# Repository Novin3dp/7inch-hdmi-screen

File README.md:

# برد راه‌انداز LCD هفت اینچ AT070TN92 با ورودی HDMI و تاچ USB

برد دولایه‌ی کوچک (۸۰×۵۰ میلی‌متر) که پشت LCD چسبانده می‌شود:

* **ورودی HDMI** (از رزبری‌پای) ← **LT8619C** ← RGB موازی ۲۴ بیتی (حالت DE) ← کانکتور FPC پنجاه‌پین **AT070TN92**
* **تاچ خازنی GT915** (روی FPC تاچ‌پنل، رابط I2C) ← **STM32F072** ← **USB HID Multi-Touch** (۵ نقطه) به رزبری‌پای
* **تغذیه‌ی کل برد از همان کابل USB-C** (۵ ولت از پورت USB رزبری‌پای)
* تولید ولتاژهای پنل روی برد: AVDD=10.4V، VGH=+16V، VGL=−6.8V، VCOM قابل تنظیم، درایور بک‌لایت جریان‌ثابت ۱۸۰ mA با PWM

> ⚠️ این طراحی کامل است و همه‌ی بررسی‌های نرم‌افزاری (DRC، تطبیق شماتیک با PCB، کامپایل فرم‌ور، اعتبارسنجی EDID) را پاس کرده، اما **هنوز ساخته و روی سخت‌افزار تست نشده است**. قبل از سفارش انبوه، یک نمونه بسازید و بخش «موارد قابل بررسی» را بخوانید.

> **نسخه‌ی DSI:** یک برد جداگانه (۶۸×۴۲ mm) هم هست که همین پنل و تاچ را مستقیم از پورت DSI رزبری‌پای و با پل ICN6211 راه می‌اندازد، بدون HDMI و بدون میکروکنترلر. طراحی در [`hardware_dsi/`](hardware_dsi/README.md) و Overlay و درایور لینوکس در `rpi_dsi/` است.
>
> **نسخه‌ی دو-میکرو:** همین برد HDMI با یک جای نصب LQFP-48 که هم STM32F072 و هم CH32X035C8T6 رویش می‌نشیند: [`hardware_dual/`](hardware_dual/README.md).
>
> **نسخه‌ی STM32F042F6P6:** همین برد HDMI با میکروی کوچک‌تر TSSOP-20 در [`hardware_f042/`](hardware_f042/README.md). فرم‌ور با `make BOARD=f042` ساخته می‌شود.

---

## ۱) بلوک دیاگرام

```
 HDMI-A ──TMDS──► LT8619C ──RGB888 + DE + PCLK──► J3 (FPC 50P) ──► AT070TN92
   │ DDC/HPD        ▲ I2C1 (0x32)                       ▲ AVDD/VGH/VGL/VCOM, VLED
   └─(EDID روی تراشه)│                                    │
                    STM32F072 ──── BIAS_EN ──► TPS61040 + پمپ‌های بار + LM321 (VCOM)
 USB-C ◄──USB FS──► │ ──── BL_PWM ───► TPS61165 (بک‌لایت ۱۸۰mA)
   │5V              │ ──── I2C2 ────► J4 (FPC 6P) ──► تاچ‌پنل GT915
   └► PTC ► AMS1117-3.3 / AMS1117-1.8 (+ فیلتر فریت برای تغذیه‌های آنالوگ LT8619C)
```

| بخش | قطعه | توضیح |
|---|---|---|
| گیرنده HDMI | LT8619C (QFN76) | کریستال 25MHz، EDID داخلی 800×480@60 که میکرو بارگذاری می‌کند؛ VTERM/VCCA33 و 1.8V آنالوگ با فریت جدا شده‌اند |
| میکرو | STM32F072CBT6 | USB بدون کریستال (HSI48 + CRS)، بوت‌لودر DFU داخلی |
| بایاس پنل | TPS61040 + 2×BAT54S + زنر | AVDD 10.4V، VGH 16V (دوبرابرکننده)، VGL −6.8V (معکوس‌کننده) |
| VCOM | LM321 + تریمر 10k (RV1) | محدوده 2.55 تا 4.5 ولت، برای کمترین فلیکر تنظیم شود |
| بک‌لایت | TPS61165 | 0.2V / 1.1Ω = 182mA، PWM با فرکانس 20kHz |
| تغذیه | AMS1117-3.3 و AMS1117-1.8 | هر دو از 5V؛ 1.8V با فریت به تغذیه‌های آنالوگ |

---

## ۲) ساختار ریپازیتوری

```
hardware/                 پروژه‌ی KiCad (نسخه 7)
  lcd_board.kicad_pro/.kicad_sch/.kicad_pcb    پروژه، شماتیک سلسله‌مراتبی (۴ صفحه)، PCB
  lcd_board.pretty/       فوت‌پرینت‌های اختصاصی (QFN76 لونتیوم، FPC پنجاه‌پین)
  lcd_board.kicad_sym     سمبل LT8619C
  fab/                    فایل‌های ساخت: gerber.zip، BOM و CPL برای JLCPCB
  gen/                    اسکریپت‌هایی که کل طراحی را می‌سازند (منبع اصلی = design.py)
firmware/                 فرم‌ور STM32F072 (C + TinyUSB)
hardware_dual/            همین برد HDMI با جای نصب مشترک STM32F072 / CH32X035C8T6
hardware_f042/            همین برد HDMI با STM32F042F6P6 — پروژه‌ی KiCad جدا با README خودش
hardware_dsi/             نسخه‌ی DSI (ICN6211) — پروژه‌ی KiCad جدا با README خودش
rpi_dsi/                  Device Tree Overlay و اسکریپت ساخت درایور ICN6211 برای نسخه‌ی DSI
docs/                     schematic.pdf، schematic_f042.pdf، schematic_dsi.pdf و تصاویر برد
*.pdf                     دیتاشیت‌ها
```

**منبع اصلی طراحی فایل `hardware/gen/design.py` است** (لیست قطعات و همه‌ی اتصالات). شماتیک، PCB و BOM از روی آن ساخته می‌شوند و `verify_netlist.py` تطابق شماتیک و طراحی را بررسی می‌کند. البته می‌توانید فایل‌های KiCad را مستقیم هم ویرایش کنید.

---

## ۳) مشخصات PCB

| مورد | مقدار |
|---|---|
| ابعاد | 80 × 50 mm، گوشه‌های گرد R2 |
| لایه | ۲ لایه، FR4، ضخامت پیشنهادی 1.0 یا 1.6 mm، مس 1oz |
| حداقل ترک/فاصله | 0.15 / 0.15 mm (تغذیه 0.25 و 0.5 mm) |
| ویا | سوراخ 0.3 / قطر 0.6 mm (ظرفیت استاندارد JLCPCB) |
| قطعات | **فقط روی رو (Top)**؛ پشت برد صاف است برای چسب دوطرفه |
| زمین | GND به‌صورت نت کامل مسیریابی شده + پور GND روی هر دو لایه + ~۳۰۰ ویای دوخت |
| DRC | **۰ خطای الکتریکی/فاصله و ۰ اتصال باز**؛ برچسب‌های سیلک بدون تداخل (هشدار فقط برای خطوط سیلک کانکتورهای لبه‌ی برد که سازنده برش می‌دهد) |
| سیلک‌اسکرین | برچسب‌ها با ارتفاع 0.8mm خودکار کنار هر قطعه گذاشته شده‌اند، روی پد/بدنه‌ی قطعه یا برچسب دیگر نمی‌افتند. ۱۳ برچسب در نواحی خیلی شلوغ جا نشدند و فقط در نقشه‌ی مونتاژ (`docs/img/pcb_assembly.png`) آمده‌اند |

نکات چیدمان:
* زوج‌های TMDS (HDMI) دستی و کوتاه (~۱۲ mm) کشیده شده‌اند و زیرشان لایه‌ی پشت زمین یکپارچه است. سرعت هر کانال برای 800×480 فقط 333Mbps است.
* خازن‌های دکاپلینگ پایه‌های VTERM/VCCA33 بین زوج‌های TMDS قرار گرفته‌اند.
* ترتیب پایه‌های RGB در LT8619C نسبت به FPC پنل وارونه است؛ گذرگاه RGB با ویا روی دو لایه جابه‌جا شده (بدون نیاز به رجیستر نامستند جابه‌جایی بیت).

---

## ۴) نصب مکانیکی و جهت FPC (مهم)

* FPC پنل (۳۰ میلی‌متر) از لبه‌ی پایین LCD به پشت تا می‌شود و از **لبه‌ی پایین برد** وارد J3 می‌شود. کنتاکت‌های FPC در این حالت رو به بالا (دور از برد) هستند، پس J3 باید **کانکتور Top-contact** باشد — همان چیزی که دیتاشیت Innolux پیشنهاد کرده: `Hirose FH12A-50S-0.5SH`.
* شماره‌ی پدهای J3 دقیقاً برابر شماره‌ی پین‌های FPC پنل است؛ **پین ۱ سمت راست** است (برد از رو، FPC از پایین وارد شود). همین جهت برای حالت تا‌نخورده (برد زیر پنل) هم درست است.
* برد را با **چسب دوطرفه‌ی فومی عایق** (۱ میلی‌متر) پشت پنل بچسبانید؛ پشت پنل فلزی است و ویاها با سولدرماسک پوشیده‌اند ولی عایق اضافه لازم است.
* J4 (FPC شش‌پین 0.5mm تاچ) هم روی لبه‌ی پایین است. ترتیب پین‌ها طبق مدار مرجع Goodix: `1 GND, 2 VDD(3.3V), 3 INT, 4 SCL, 5 SDA, 6 RST`. **ترتیب پین FPC تاچ‌پنل خودتان را حتماً چک کنید**؛ اگر فرق دارد، به یک تبدیل FPC یا تغییر ترتیب پین‌های J4 در `design.py` نیاز است.
* HDMI از لبه‌ی چپ و USB-C از لبه‌ی راست خارج می‌شوند.

---

## ۵) تغذیه و مصرف

| مصرف‌کننده | تقریبی |
|---|---|
| بک‌لایت (9.3V × 180mA ÷ راندمان) | ~2.0 W |
| LT8619C (1.8V و 3.3V، از LDO) | ~1.1 W از 5V |
| بایاس پنل + منطق + میکرو + تاچ | ~0.4 W |
| **جمع** | **~3.5 W ≈ 0.7 A از 5V** |

پورت‌های USB رزبری‌پای ۴ و ۵ این جریان را می‌دهند (مجموعاً 1.2A/1.6A). با کم کردن نور بک‌لایت مصرف کم می‌شود. فیوز PTC (1.1A) روی VBUS است.

ترتیب روشن شدن (طبق بخش 3.2 دیتاشیت پنل، توسط فرم‌ور):
`DVDD(3.3V) → آزاد شدن RESET → BIAS_EN (VGL و AVDD، سپس VGH با تأخیر RC) → داده‌ی تصویر → بعد از 200ms بک‌لایت`.
بک‌لایت فقط وقتی تصویر معتبر از HDMI دریافت می‌شود روشن است.

---

## ۶) ساخت برد (JLCPCB)

1. `hardware/fab/lcd_board_gerbers.zip` را برای ساخت PCB آپلود کنید (2 لایه).
2. برای مونتاژ: `hardware/fab/bom_jlcpcb.csv` و `hardware/fab/cpl_jlcpcb.csv`.
   * شماره‌های LCSC فقط برای قطعاتی که مطمئن بودم پر شده‌اند؛ بقیه را با MPN/مقدار جستجو کنید.
   * LT8619C معمولاً در LCSC نیست؛ از فروشنده‌های لونتیوم (مثلاً بازار چین) تهیه و دستی لحیم کنید (QFN76 با پد زیرین: هیتر هوای گرم/استنسیل).
   * چرخش‌ها در CPL را در پیش‌نمایش JLC کنترل کنید.
3. قطعات نصب‌نشده (DNP): J5 (هدر SWD/UART)، نقاط تست TP1..TP8.
4. همه‌ی مقاومت‌ها و خازن‌های کوچک پکیج **0603** هستند (لحیم دستی راحت). فقط چند خازن که به ظرفیت/ولتاژ بالا نیاز دارند 0805/1206 مانده‌اند (22µF، 4.7µF/25V، 1µF/50V، 2.2µF/50V) و مقاومت حسگر جریان بک‌لایت 0805 است.

---

## ۷) فرم‌ور

```sh
cd firmware
./fetch_deps.sh        # TinyUSB 0.17 + هدرهای CMSIS
make                   # نیاز به arm-none-eabi-gcc ؛ خروجی build/lcd_touch.bin
make flash-dfu         # دکمه‌ی BOOT را نگه دارید و USB را وصل کنید (dfu-util لازم است)
```

برای برد دو-میکرو با CH32X035C8T6: `./fetch_deps.sh ch32 && make BOARD=ch32` (جزئیات در `hardware_dual/README.md`). برای برد F042: `make BOARD=f042`.

کارهایی که فرم‌ور انجام می‌دهد:
* ترتیب روشن شدن پنل و کنترل بک‌لایت
* راه‌اندازی LT8619C: ریست، خواندن Chip ID (0x16 0x04)، بارگذاری EDID (800×480@60Hz، 33.26MHz)، HPD، پیکربندی گیرنده و خروجی RGB888 SDR، تبدیل رنگ YCbCr→RGB، کپی تایمینگ ورودی به خروجی
* انتخاب آدرس GT915 (0x5D) با ترتیب INT/RESET دیتاشیت، خواندن رزولوشن تنظیم‌شده‌ی تاچ و مقیاس‌کردن به 800×480
* دستگاه USB HID «Touch Screen» پنج‌نقطه‌ای؛ لینوکس (hid-multitouch) بدون درایور اضافه می‌شناسد
* کنسول UART (پین‌های 5 و 6 هدر J5، 115200): دستورات `status`، `bl 0..100`، `phase 0..9`، `rot 0|1`، `swap`، `invx`، `invy`، `save`
* تنظیمات (نور، چرخش ۱۸۰ درجه، جهت تاچ، فاز PCLK) در فلش ذخیره می‌شوند

---

## ۸) تنظیم رزبری‌پای

با Raspberry Pi OS (KMS) معمولاً هیچ تنظیمی لازم نیست: EDID برد حالت 800×480 را اعلام می‌کند و تاچ به‌صورت خودکار شناخته می‌شود. اگر تصویر نیامد، در `/boot/firmware/cmdline.txt` اضافه کنید:

```
video=HDMI-A-1:800x480M@60
```

و برای Pi های قدیمی (درایور غیر KMS) در `config.txt`:

```
hdmi_group=2
hdmi_mode=87
hdmi_cvt=800 480 60 6 0 0 0
hdmi_drive=1
```

برای چرخاندن ۱۸۰ درجه بهتر است از دستور `rot 1` کنسول برد استفاده کنید (پنل و تاچ هر دو در سخت‌افزار برمی‌گردند).

---

## ۹) موارد قابل بررسی و ریسک‌ها (لطفاً بخوانید)

1. **LT8619C سند رسمی رجیستر ندارد.** توالی رجیسترها از درایورهای متن‌باز (Hardkernel u-boot و درایور V4L2 راک‌چیپ) گرفته شده و برای خروجی RGB888 کار کرده است. اگر رنگ‌ها لرزش/نویز داشتند فاز PCLK را با `phase 0..9` تغییر دهید. برای تولید، از Lontium (support@lontium.com) شماتیک مرجع و Programming Guide بخواهید.
2. در گزارش موجود در ریپازیتوری گفته شده که خطوط TMDS با خازن 100nF کوپل AC شوند؛ **این برای HDMI درست نیست** — TMDS کوپل DC است و ترمینیشن به 3.3V از پایه‌های VTERM می‌آید. در این برد اتصال مستقیم است.
3. جهت FPC پنل و نوع کانکتور Top-contact (بخش ۴) را قبل از لحیم کنترل کنید.
4. ترتیب پین FPC تاچ‌پنل شما ممکن است با ترتیب مرجع Goodix فرق داشته باشد.
5. GT915 برای پنل‌های ۴.۵ تا ۶ اینچ طراحی شده؛ پیکربندی (Config) آن را سازنده‌ی تاچ‌پنل در فلش آی‌سی ذخیره کرده است. اگر محورها برعکس بود با `swap/invx/invy` اصلاح کنید.
6. VCOM هر پنل باید با RV1 برای کمترین فلیکر تنظیم شود (نقطه‌ی تست TP7). مقدار معمول طبق دیتاشیت ~3.6V.
7. محافظ ESD روی خطوط TMDS عمداً حذف شده تا مسیرها کوتاه و تمیز بمانند (سیگنال‌ها مستقیم به LT8619C می‌روند).
8. پین‌اوت آی‌سی‌ها از کتابخانه‌ی رسمی KiCad برداشته شده و پین‌اوت TPS61040 و TPS61165 با دیتاشیت TI چک شد؛ فوت‌پرینت QFN76 از ابعاد صفحه 16 دیتاشیت LT8619C ساخته شده (پد زیرین 5.81×6.31mm).
9. VID/PID USB از `pid.codes` (آزمایشی 1209:0001) است؛ برای محصول تجاری عوض کنید.

---

## ۱۰) ساخت دوباره‌ی طراحی از اسکریپت‌ها

نیازمندی‌ها: KiCad 7 (`kicad-cli` و ماژول پایتون `pcbnew`)، Java و Xvfb برای Freerouting.

```sh
cd hardware/gen
python3 make_libs.py                 # فوت‌پرینت/سمبل اختصاصی
python3 gen_sch.py                   # شماتیک
python3 verify_netlist.py            # تطبیق شماتیک با design.py
python3.12 pcb.py                    # چیدمان + مسیرهای دستی (TMDS، USB، VCOM، I2C و تغذیه آنالوگ LT8619C)
python3.12 route.py export           # فایل DSN برای Freerouting
java -jar freerouting-2.0.1.jar --gui.enabled=false -de ../lcd_board.dsn -do ../lcd_board.ses -mp 100
python3.12 route.py import ../lcd_board.ses   # مسیرها + پورها + ویاهای دوخت
python3.12 check.py --fill           # پر کردن پورها و DRC
python3 fab.py                       # گربر، BOM، CPL، تصاویر و PDF شماتیک
```

فایل `hardware/lcd_board.ses` (خروجی Freerouting که برد فعلی از آن ساخته شده) در ریپازیتوری هست، پس بدون اجرای دوباره‌ی Freerouting هم `route.py import` همین برد را می‌سازد.

## مجوز

سخت‌افزار: CERN-OHL-P v2. فرم‌ور: GPL-2.0-or-later (چون توالی LT8619C از کد GPL گرفته شده).

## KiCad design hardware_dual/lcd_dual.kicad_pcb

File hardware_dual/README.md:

# HDMI7 دو-میکرو: STM32F072CBT6 یا CH32X035C8T6 روی یک جای نصب

این پروژه همان برد HDMI7 اصلی (`hardware/`، 80×50mm) است، با **USB-C در لبه‌ی چپ، درست زیر سوکت HDMI** (هر دو کابل رزبری‌پای از یک طرف خارج می‌شوند؛ آی‌سی ESD یعنی U4 روی مسیر USB به سمت میکرو است)، با یک فوت‌پرینت LQFP-48 (U10) که **هر دو میکرو** روی آن می‌نشینند. اول STM32F072 را نصب و برد را تست کنید، بعد آن را با هوای گرم بردارید و CH32X035C8T6 را جایش لحیم کنید.

> ⚠️ همه‌ی بررسی‌های نرم‌افزاری پاس شده‌اند (DRC بدون خطا و بدون اتصال باز، تطبیق شماتیک با PCB، کامپایل فرم‌ور هر دو میکرو)، ولی برد و فرم‌ور CH32 **هنوز روی سخت‌افزار تست نشده‌اند**.

## چرا یک فوت‌پرینت کافی است

پایه‌های اصلی دو تراشه در LQFP-48 یکی‌اند:

| پایه | STM32F072 | CH32X035C8T6 |
|---|---|---|
| 7 | NRST | PA21/RST |
| 32 / 33 | USB D− / D+ | USB D− / D+ |
| 34 / 37 | SWDIO / SWCLK | SWDIO / SWCLK |
| 47 / 48 | VSS / VDD | GND / VDD |

همه‌ی سیگنال‌های برد روی CH32 هم به یک GPIO قابل استفاده می‌رسند:

| پایه | سیگنال | STM32F072 | CH32X035 |
|---|---|---|---|
| 10 | HDMI5V_DET | PA0 | PA0 |
| 16 | BL_PWM | PA6 (TIM3_CH1) | PA6 (TIM3_CH1) |
| 18 / 19 / 20 | LCD_RST / LR / UD | PB0 / PB1 / PB2 | PC6 / PC7 / PB0 |
| 21 / 22 | TP_SCL / TP_SDA | PB10 / PB11 (I2C2) | PB1 / PB2 (I2C نرم‌افزاری) |
| 25 / 26 | TP_INT / TP_RST | PB12 / PB13 | PB5 / PB6 |
| 28 / 29 | LED / BIAS_EN | PB15 / PA8 | PB8 / PB9 |
| 30 / 31 | UART TX / RX | PA9 / PA10 (USART1) | PB10 / PB11 (USART1) |
| 41 | LT_RSTN | PB5 | PA9 |
| 42 / 43 | LT_SCL / LT_SDA | PB6 / PB7 (I2C1) | PA10 / PA11 (I2C نرم‌افزاری) |
| 44 | BOOT0 | BOOT0 | PA12 (استفاده نمی‌شود) |

I2C روی CH32 نرم‌افزاری است، چون I2C سخت‌افزاری آن در بعضی سری‌های تولید ایراد دارد.

**نکته‌ی مهم برای فرم‌ور CH32:** پایه‌های تغذیه‌ی STM32 (۱، ۸، ۹، ۲۳، ۲۴، ۳۵، ۳۶) روی CH32 پایه‌ی GPIO هستند (PA15، PA22، PA23، PB3، PB4، PB12، PB13) که به 3.3V یا زمین وصل شده‌اند. فرم‌ور CH32 **هرگز نباید این پایه‌ها را خروجی کند**؛ بعد از ریست ورودی هستند و همین‌طور باید بمانند.

## بوت‌لودر

* **STM32F072:** دکمه‌ی SW1 (BOOT0) را نگه دارید و USB را وصل کنید ← DFU.
* **CH32X035:** دکمه‌ی SW2 را نگه دارید و USB را وصل کنید. SW2 پایه‌ی D+ (PC17) را از طریق R38 (4.7k) به 3.3V می‌برد و تراشه وارد بوت‌لودر USB می‌شود (WCHISPTool یا `wchisp`). برنامه‌ریزی با WCH-LinkE روی هدر J5 (SWDIO/SWCLK) هم ممکن است. SW2 روی STM32 بی‌اثر است.

## فرم‌ور

هر دو میکرو از همان کد `firmware/` استفاده می‌کنند؛ فقط لایه‌ی سخت‌افزار (کلاک، GPIO، PWM، UART، فلش، I2C) جداست (`firmware/src/stm32/` و `firmware/src/ch32/`).

```sh
cd firmware
./fetch_deps.sh ch32          # SDK رسمی WCH (EVT) + TinyUSB master (درایور USB برای CH32X035)
make                          # STM32F072  -> build/lcd_touch.bin
make BOARD=ch32               # CH32X035C8T6 -> build_ch32/lcd_touch_ch32.bin  (28.9KB فلش، ~5KB رم)
make BOARD=ch32 flash-isp     # بوت‌لودر USB (SW2 را هنگام وصل کردن USB نگه دارید)، با wchisp
make BOARD=ch32 flash-wlink   # یا با WCH-LinkE روی J5
```

کامپایلر RISC-V لازم است: `riscv-none-elf-gcc` (xPack) یا در اوبونتو `gcc-riscv64-unknown-elf` + `picolibc-riscv64-unknown-elf`.

تفاوت‌های نسخه‌ی CH32:
* هر دو باس I2C نرم‌افزاری (bit-bang) هستند: LT8619C حدود 100kHz و GT915 حدود 250kHz، با پشتیبانی از clock stretching و آزادسازی باس گیرکرده در شروع.
* USB: کنترلر USBFS داخلی، بدون کریستال، مقاومت pull-up داخلی روی D+ و PHY در حالت 3.3V.
* تنظیمات در آخرین صفحه‌ی ۲۵۶ بایتی فلش (0x0800F700) ذخیره می‌شوند.
* دستورهای کنسول (`status`، `bl`، `phase`، `rot`، ...) و رفتار برد همان نسخه‌ی STM32 است.

## تعویض میکرو

1. با STM32F072 و فرم‌ور `firmware/` (`make`) برد را کامل تست کنید.
2. STM32 را با هوای گرم بردارید، پدها را با فتیله تمیز کنید.
3. CH32X035C8T6 را با **همان جهت پایه‌ی ۱** لحیم کنید.

## بک‌لایت: TPS61169DCKR

در این برد درایور بک‌لایت **TPS61169DCKR** (پکیج SC70-5) است، به‌جای TPS61165 در برد اصلی:

| مورد | مقدار |
|---|---|
| پایه‌ها | 1 SW، 2 GND، 3 FB، 4 CTRL، 5 VIN |
| جریان LED | 204mV / R31 (1.13Ω) ≈ **۱۸۰mA** |
| PWM روشنایی | 20kHz از میکرو روی CTRL (مجاز طبق دیتاشیت: 5 تا 100kHz) |
| خاموشی | CTRL بیش از 2.5ms پایین ← خاموش |
| قطعات اطراف | سلف 10µH (مجاز 4.7 تا 10µH)، دیود MBR0560، خازن خروجی 2.2µF/50V (مجاز 1 تا 10µF) |

خازن جبران‌سازی (C44 در برد اصلی) حذف شده، چون TPS61169 جبران‌سازی داخلی دارد. فرم‌ور تغییری لازم ندارد.

## ساخت

**ویاها:** همه‌ی ۴۶۳ ویا سوراخ 0.4mm و قطر بیرونی 0.7mm هستند (حلقه‌ی مسی 0.15mm). ویاهای حرارتی زیر LT8619C جزء فوت‌پرینت‌اند و همان 0.3/0.6 مانده‌اند.

`fab/lcd_dual_gerbers.zip`، `fab/bom_jlcpcb.csv` (با STM32F072)، `fab/cpl_jlcpcb.csv`؛ شماتیک: `docs/schematic_dual.pdf`. برای ساخت دوباره، اسکریپت‌های `hardware_dual/gen` مثل بخش ۱۰ README اصلی اجرا می‌شوند.

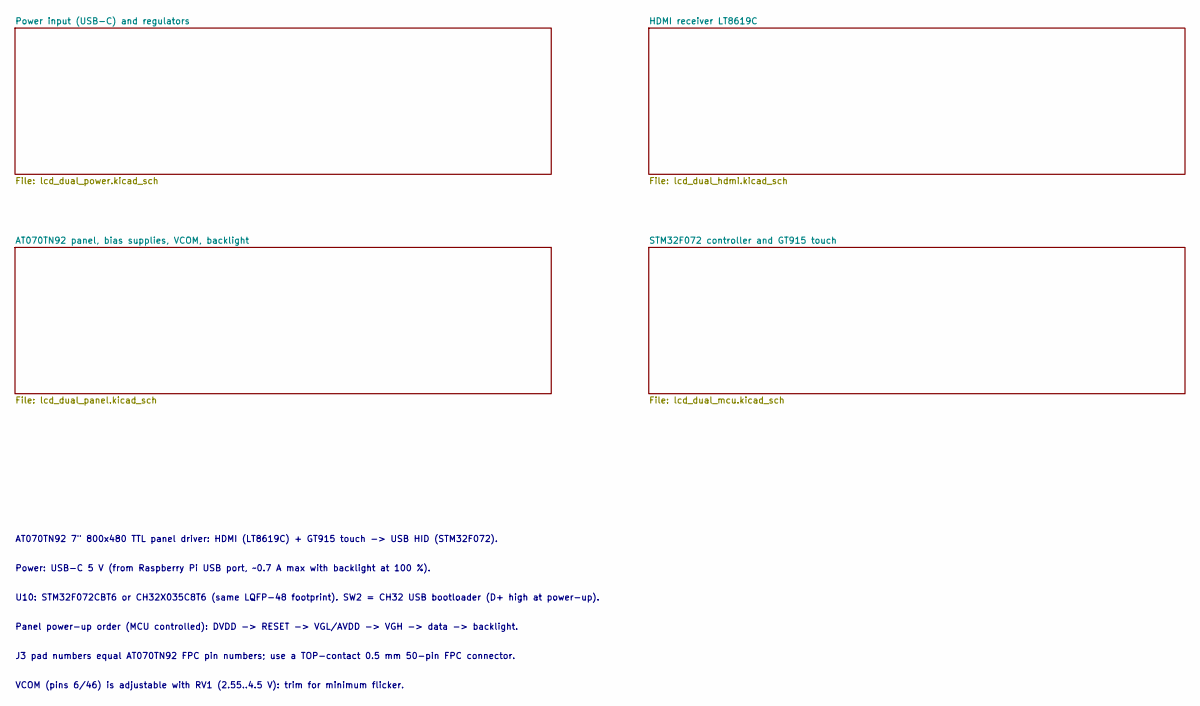
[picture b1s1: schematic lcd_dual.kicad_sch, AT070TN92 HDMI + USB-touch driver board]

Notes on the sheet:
AT070TN92 7" 800x480 TTL panel driver: HDMI (LT8619C) + GT915 touch -> USB HID (STM32F072).
Power: USB-C 5 V (from Raspberry Pi USB port, ~0.7 A max with backlight at 100 %).
U10: STM32F072CBT6 or CH32X035C8T6 (same LQFP-48 footprint). SW2 = CH32 USB bootloader (D+ high at power-up).
Panel power-up order (MCU controlled): DVDD -> RESET -> VGL/AVDD -> VGH -> data -> backlight.
J3 pad numbers equal AT070TN92 FPC pin numbers; use a TOP-contact 0.5 mm 50-pin FPC connector.
VCOM (pins 6/46) is adjustable with RV1 (2.55..4.5 V): trim for minimum flicker.

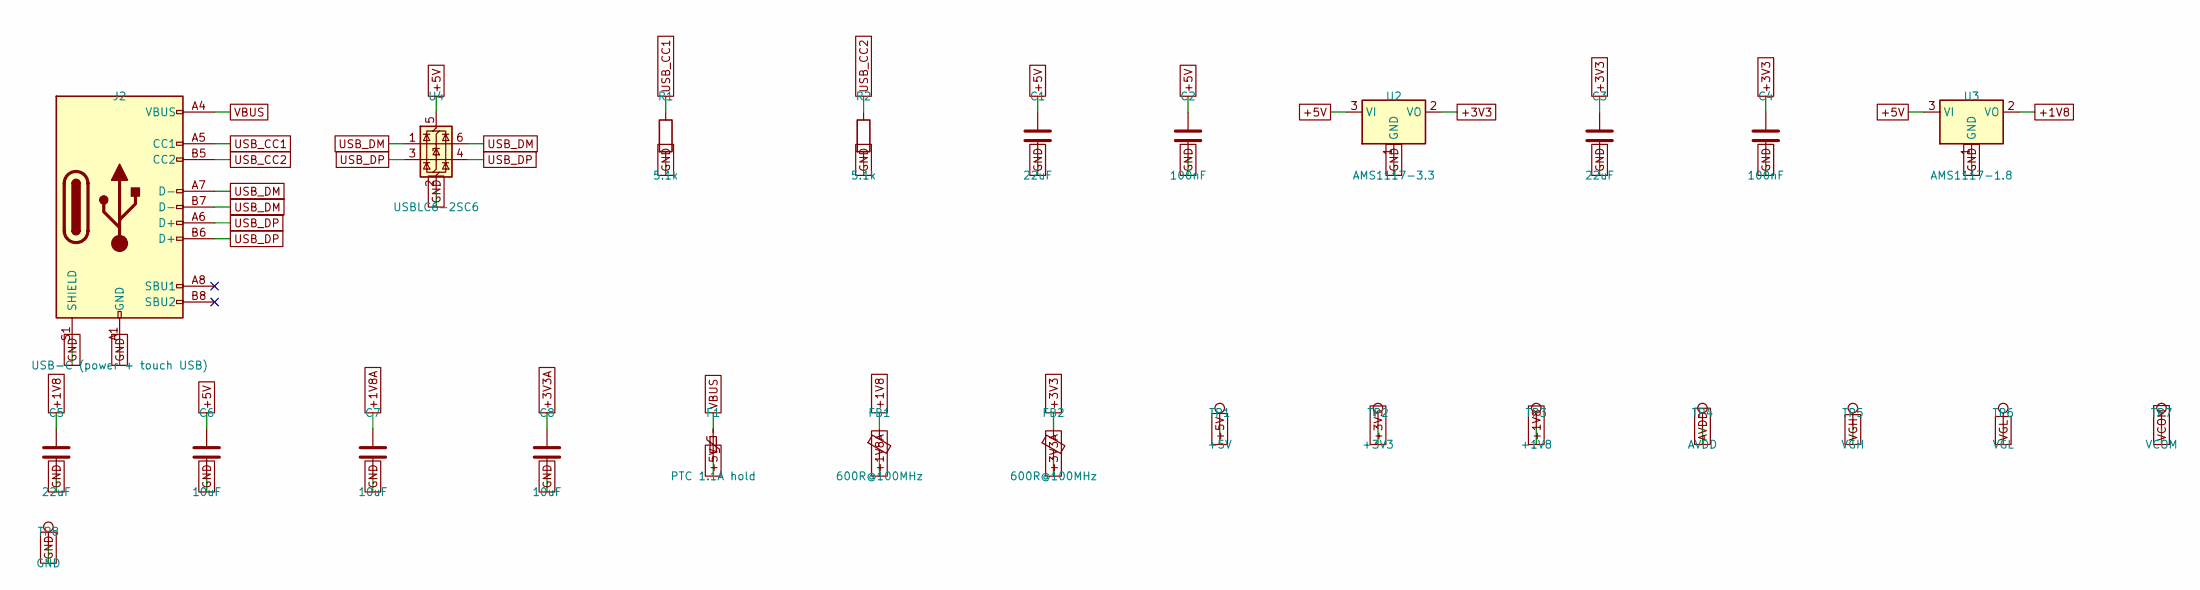
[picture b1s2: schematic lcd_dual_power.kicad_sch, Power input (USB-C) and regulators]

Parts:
C1, C3, C5: 22uF; C_0805_2012Metric
C2, C4: 100nF; C_0603_1608Metric; LCSC C14663
C6, C7, C8: 10uF; C_0603_1608Metric; LCSC C19702
F1: PTC 1.1A hold; Fuse_1206_3216Metric; MPN 1206L110/16 (or BSMD1206-110)
FB1, FB2: 600R@100MHz; L_0603_1608Metric; MPN BLM18PG601SN1D
J2: USB-C (power + touch USB); USB_C_Receptacle_HRO_TYPE-C-31-M-12; MPN HRO TYPE-C-31-M-12; LCSC C165948
R1, R2: 5.1k; R_0603_1608Metric; LCSC C23186
TP1: +5V; TestPoint_Pad_D1.0mm
TP2: +3V3; TestPoint_Pad_D1.0mm
TP3: +1V8; TestPoint_Pad_D1.0mm
TP4: AVDD; TestPoint_Pad_D1.0mm
TP5: VGH; TestPoint_Pad_D1.0mm
TP6: VGL; TestPoint_Pad_D1.0mm
TP7: VCOM; TestPoint_Pad_D1.0mm
TP8: GND; TestPoint_Pad_D1.0mm
U2: AMS1117-3.3; SOT-223-3_TabPin2; MPN AMS1117-3.3; LCSC C6186
U3: AMS1117-1.8; SOT-223-3_TabPin2; MPN AMS1117-1.8
U4: USBLC6-2SC6; SOT-23-6; MPN USBLC6-2SC6; LCSC C7519

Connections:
+1V8: C5.1, FB1.1, TP3.1, U3.2 (VO); also elsewhere on the board
+1V8A: C7.1, FB1.2; also elsewhere on the board
+3V3: C3.1, C4.1, FB2.1, TP2.1, U2.2 (VO); also elsewhere on the board
+3V3A: C8.1, FB2.2; also elsewhere on the board
+5V: C1.1, C2.1, C6.1, F1.2, TP1.1, U2.3 (VI), U3.3 (VI), U4.5 (VBUS); also elsewhere on the board
AVDD: TP4.1; also elsewhere on the board
GND: C1.2, C2.2, C3.2, C4.2, C5.2, C6.2, C7.2, C8.2, J2.A1 (GND), J2.A12 (GND), J2.B1 (GND), J2.B12 (GND), J2.S1 (SHIELD), R1.2, R2.2, TP8.1, U2.1 (GND), U3.1 (GND), U4.2 (GND); also elsewhere on the board
USB_CC1: J2.A5 (CC1), R1.1
USB_CC2: J2.B5 (CC2), R2.1
USB_DM: J2.A7 (D-), J2.B7 (D-), U4.1 (I/O1), U4.6 (I/O1); also elsewhere on the board
USB_DP: J2.A6 (D+), J2.B6 (D+), U4.3 (I/O2), U4.4 (I/O2); also elsewhere on the board
VBUS: F1.1, J2.A4 (VBUS), J2.A9 (VBUS), J2.B4 (VBUS), J2.B9 (VBUS)
VCOM: TP7.1; also elsewhere on the board
VGH: TP5.1; also elsewhere on the board
VGL: TP6.1; also elsewhere on the board

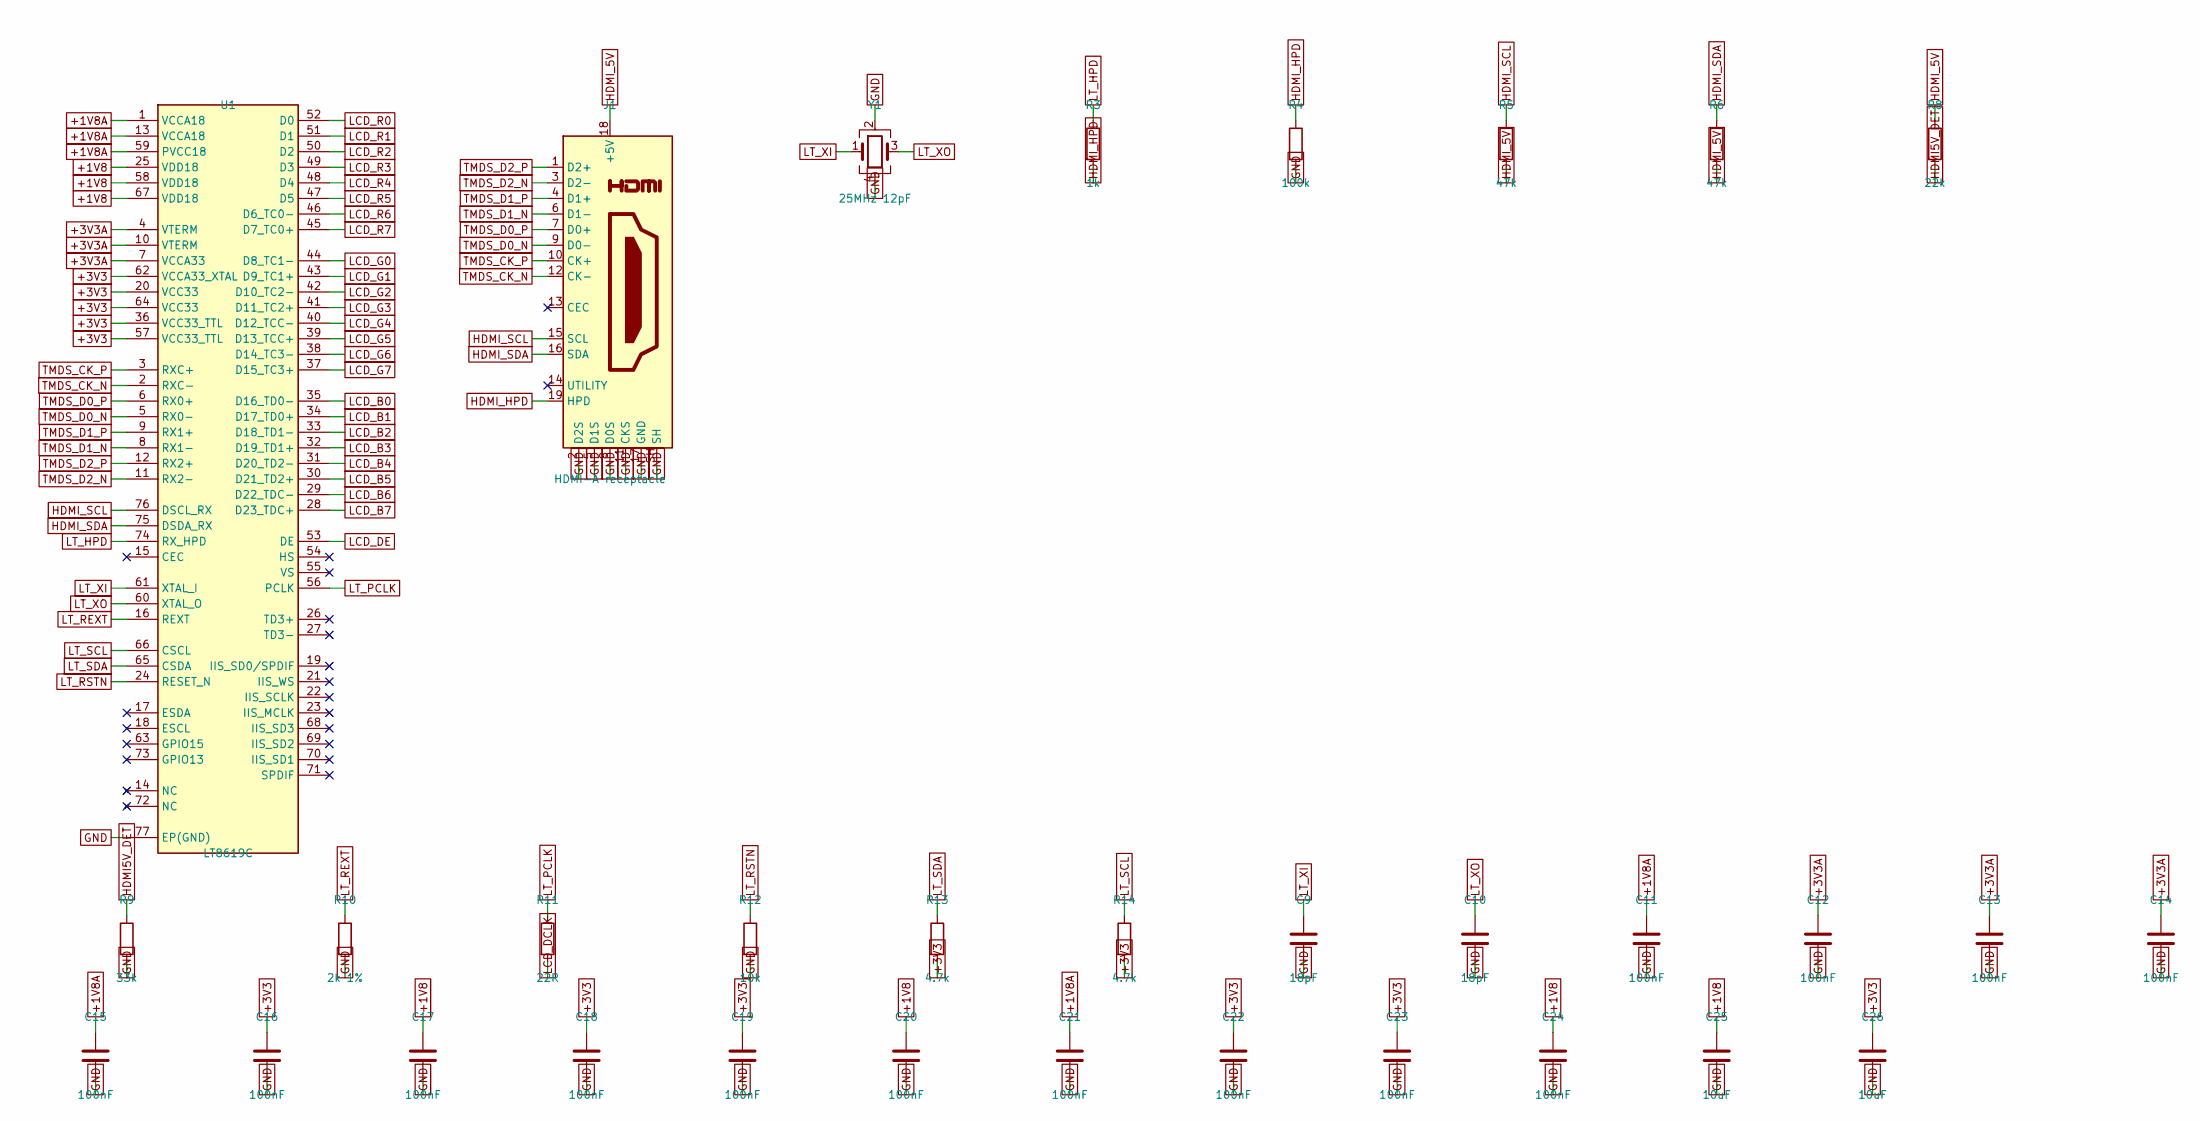
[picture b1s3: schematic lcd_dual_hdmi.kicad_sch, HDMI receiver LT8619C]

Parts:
C9, C10: 18pF; C_0603_1608Metric
C11, C12, C13, C14, C15, C16, C17, C18, C19, C20, C21, C22, C23, C24: 100nF; C_0603_1608Metric; LCSC C14663
C25, C26: 10uF; C_0603_1608Metric; LCSC C19702
J1: HDMI-A receptacle; HDMI_A_Amphenol_10029449-x01xLF_Horizontal; MPN Amphenol 10029449-001RLF (or equivalent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
R3: 1k; R_0603_1608Metric; LCSC C21190
R4: 100k; R_0603_1608Metric; LCSC C25803
R5, R6: 47k; R_0603_1608Metric
R8: 22k; R_0603_1608Metric
R9: 33k; R_0603_1608Metric
R10: 2k 1%; R_0603_1608Metric
R11: 22R; R_0603_1608Metric
R12: 10k; R_0603_1608Metric; LCSC C25804
R13, R14: 4.7k; R_0603_1608Metric; LCSC C23162
U1: LT8619C; Lontium_QFN-76_9x9mm_P0.4mm_EP5.81x6.31mm; MPN LT8619C (Lontium)
Y1: 25MHz 12pF; Crystal_SMD_3225-4Pin_3.2x2.5mm; MPN X322525MOB4SI (25MHz CL=12pF)

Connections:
+1V8: C17.1, C20.1, C24.1, C25.1, U1.25 (VDD18), U1.58 (VDD18), U1.67 (VDD18); also elsewhere on the board
+1V8A: C11.1, C15.1, C21.1, U1.1 (VCCA18), U1.13 (VCCA18), U1.59 (PVCC18); also elsewhere on the board
+3V3: C16.1, C18.1, C19.1, C22.1, C23.1, C26.1, R13.2, R14.2, U1.20 (VCC33), U1.36 (VCC33_TTL), U1.57 (VCC33_TTL), U1.62 (VCCA33_XTAL), U1.64 (VCC33); also elsewhere on the board
+3V3A: C12.1, C13.1, C14.1, U1.4 (VTERM), U1.7 (VCCA33), U1.10 (VTERM); also elsewhere on the board
GND: C9.2, C10.2, C11.2, C12.2, C13.2, C14.2, C15.2, C16.2, C17.2, C18.2, C19.2, C20.2, C21.2, C22.2, C23.2, C24.2, C25.2, C26.2, J1.2 (D2S), J1.5 (D1S), J1.8 (D0S), J1.11 (CKS), J1.17 (GND), J1.SH, R4.2, R9.2, R10.2, R12.2, U1.77 (EP(GND)), Y1.2, Y1.4; also elsewhere on the board
HDMI5V_DET: R8.2, R9.1; also elsewhere on the board
HDMI_5V: J1.18 (+5V), R5.2, R6.2, R8.1
HDMI_HPD: J1.19 (HPD), R3.2, R4.1
HDMI_SCL: J1.15 (SCL), R5.1, U1.76 (DSCL_RX)
HDMI_SDA: J1.16 (SDA), R6.1, U1.75 (DSDA_RX)
LCD_B0: U1.35 (D16_TD0-); also elsewhere on the board
LCD_B1: U1.34 (D17_TD0+); also elsewhere on the board
LCD_B2: U1.33 (D18_TD1-); also elsewhere on the board
LCD_B3: U1.32 (D19_TD1+); also elsewhere on the board
LCD_B4: U1.31 (D20_TD2-); also elsewhere on the board
LCD_B5: U1.30 (D21_TD2+); also elsewhere on the board
LCD_B6: U1.29 (D22_TDC-); also elsewhere on the board
LCD_B7: U1.28 (D23_TDC+); also elsewhere on the board
LCD_DCLK: R11.2; also elsewhere on the board
LCD_DE: U1.53 (DE); also elsewhere on the board
LCD_G0: U1.44 (D8_TC1-); also elsewhere on the board
LCD_G1: U1.43 (D9_TC1+); also elsewhere on the board
LCD_G2: U1.42 (D10_TC2-); also elsewhere on the board
LCD_G3: U1.41 (D11_TC2+); also elsewhere on the board
LCD_G4: U1.40 (D12_TCC-); also elsewhere on the board
LCD_G5: U1.39 (D13_TCC+); also elsewhere on the board
LCD_G6: U1.38 (D14_TC3-); also elsewhere on the board
LCD_G7: U1.37 (D15_TC3+); also elsewhere on the board
LCD_R0: U1.52 (D0); also elsewhere on the board
LCD_R1: U1.51 (D1); also elsewhere on the board
LCD_R2: U1.50 (D2); also elsewhere on the board
LCD_R3: U1.49 (D3); also elsewhere on the board
LCD_R4: U1.48 (D4); also elsewhere on the board
LCD_R5: U1.47 (D5); also elsewhere on the board
LCD_R6: U1.46 (D6_TC0-); also elsewhere on the board
LCD_R7: U1.45 (D7_TC0+); also elsewhere on the board
LT_HPD: R3.1, U1.74 (RX_HPD)
LT_PCLK: R11.1, U1.56 (PCLK)
LT_REXT: R10.1, U1.16 (REXT)
LT_RSTN: R12.1, U1.24 (RESET_N); also elsewhere on the board
LT_SCL: R14.1, U1.66 (CSCL); also elsewhere on the board
LT_SDA: R13.1, U1.65 (CSDA); also elsewhere on the board
LT_XI: C9.1, U1.61 (XTAL_I), Y1.1
LT_XO: C10.1, U1.60 (XTAL_O), Y1.3
TMDS_CK_N: J1.12 (CK-), U1.2 (RXC-)
TMDS_CK_P: J1.10 (CK+), U1.3 (RXC+)
TMDS_D0_N: J1.9 (D0-), U1.5 (RX0-)
TMDS_D0_P: J1.7 (D0+), U1.6 (RX0+)
TMDS_D1_N: J1.6 (D1-), U1.8 (RX1-)
TMDS_D1_P: J1.4 (D1+), U1.9 (RX1+)
TMDS_D2_N: J1.3 (D2-), U1.11 (RX2-)
TMDS_D2_P: J1.1 (D2+), U1.12 (RX2+)

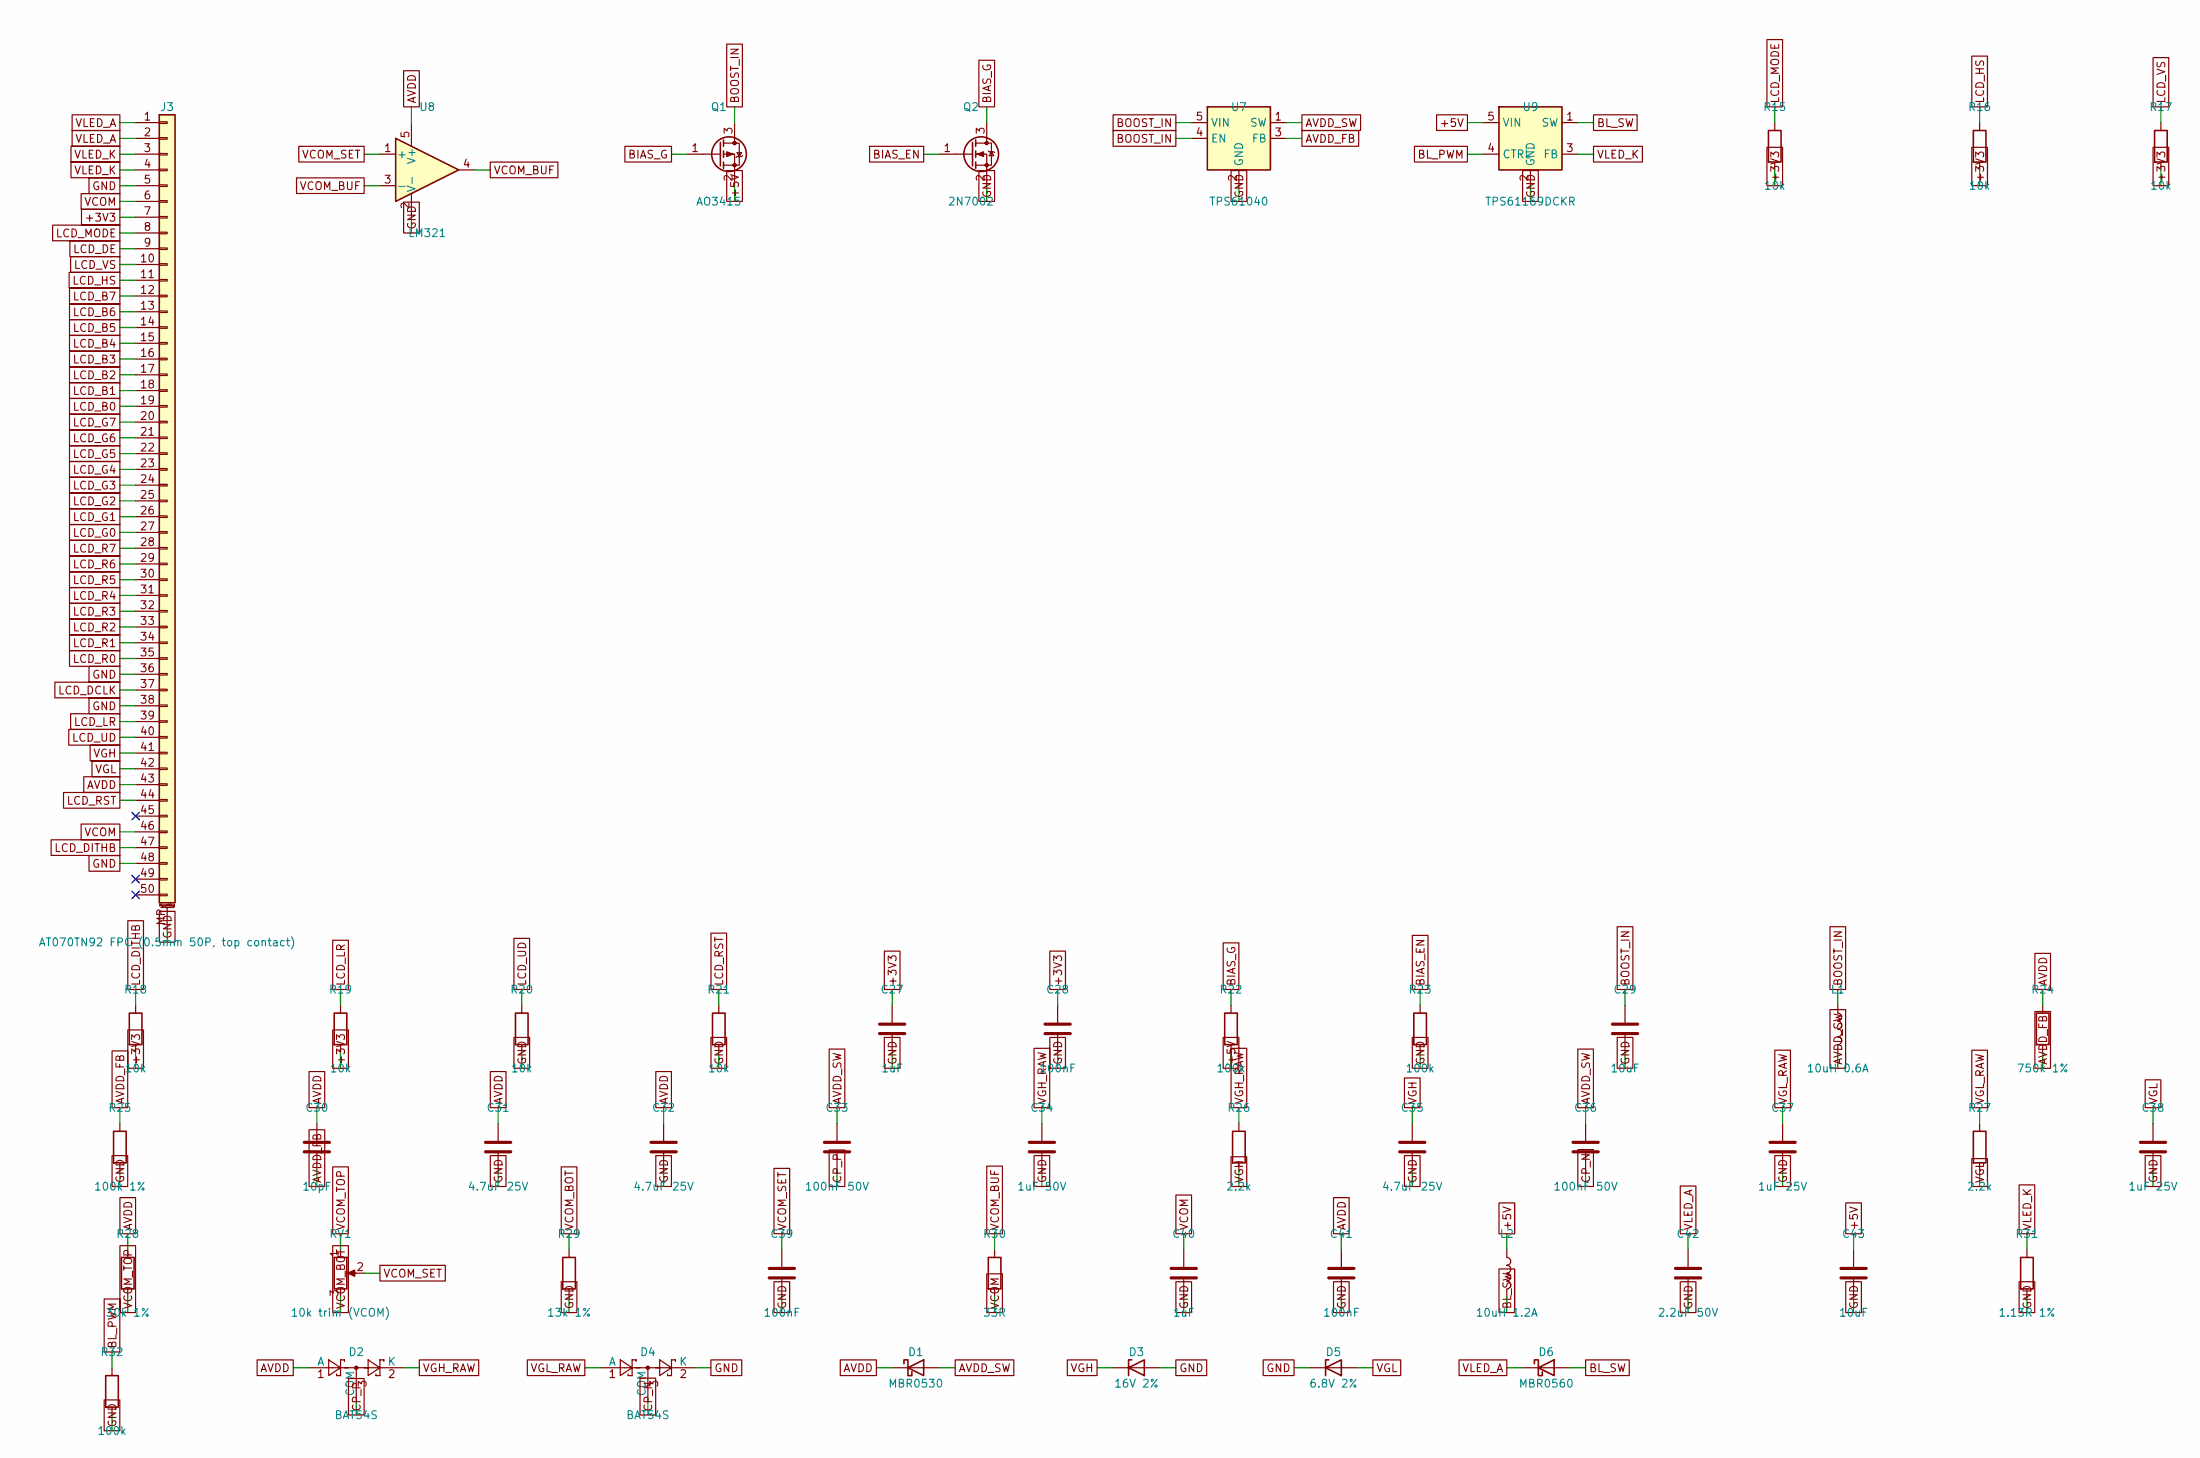
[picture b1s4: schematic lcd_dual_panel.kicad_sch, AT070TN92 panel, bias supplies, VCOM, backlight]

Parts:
C27, C40: 1uF; C_0603_1608Metric; LCSC C15849
C28, C39, C41: 100nF; C_0603_1608Metric; LCSC C14663
C29, C43: 10uF; C_0603_1608Metric; LCSC C19702
C30: 10pF; C_0603_1608Metric
C31, C32, C35: 4.7uF 25V; C_0805_2012Metric
C33, C36: 100nF 50V; C_0603_1608Metric; LCSC C14663
C34: 1uF 50V; C_0805_2012Metric
C37, C38: 1uF 25V; C_0603_1608Metric; LCSC C15849
C42: 2.2uF 50V; C_1206_3216Metric
D1: MBR0530; D_SOD-123; MPN MBR0530T1G
D2, D4: BAT54S; SOT-23; MPN BAT54S
D3: 16V 2%; D_SOD-323; MPN BZX384-B16
D5: 6.8V 2%; D_SOD-323; MPN BZX384-B6V8
D6: MBR0560; D_SOD-123; MPN MBR0560T1G
J3: AT070TN92 FPC (0.5mm 50P, top contact); FPC_50P_P0.5_TopContact_AT070TN92; MPN Hirose FH12A-50S-0.5SH(55) (top contact)
L1: 10uH 0.6A; L_Taiyo-Yuden_NR-30xx; MPN NR3015T100M
L2: 10uH 1.2A; L_Taiyo-Yuden_NR-40xx; MPN NR4018T100M
Q1: AO3415; SOT-23; MPN AO3415
Q2: 2N7002; SOT-23; MPN 2N7002; LCSC C8545
R15, R16, R17, R18, R19, R20, R21: 10k; R_0603_1608Metric; LCSC C25804
R22, R23, R32: 100k; R_0603_1608Metric; LCSC C25803
R24: 750k 1%; R_0603_1608Metric
R25: 100k 1%; R_0603_1608Metric; LCSC C25803
R26, R27: 2.2k; R_0603_1608Metric
R28: 30k 1%; R_0603_1608Metric
R29: 13k 1%; R_0603_1608Metric
R30: 33R; R_0603_1608Metric
R31: 1.13R 1%; R_0805_2012Metric
RV1: 10k trim (VCOM); Potentiometer_Bourns_TC33X_Vertical; MPN Bourns TC33X-2-103E
U7: TPS61040; SOT-23-5; MPN TPS61040DBVR
U8: LM321; SOT-23-5; MPN LM321MFX
U9: TPS61169DCKR; SOT-353_SC-70-5; MPN TPS61169DCKR

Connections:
+3V3: C27.1, C28.1, J3.7, R15.2, R16.2, R17.2, R18.2, R19.2; also elsewhere on the board
+5V: C43.1, L2.1, Q1.2 (S), R22.2, U9.5 (VIN); also elsewhere on the board
AVDD: C30.1, C31.1, C32.1, C41.1, D1.1 (K), D2.1 (A), J3.43, R24.1, R28.1, U8.5 (V+); also elsewhere on the board
AVDD_FB: C30.2, R24.2, R25.1, U7.3 (FB)
AVDD_SW: C33.1, C36.1, D1.2 (A), L1.2, U7.1 (SW)
BIAS_EN: Q2.1 (G), R23.1; also elsewhere on the board
BIAS_G: Q1.1 (G), Q2.3 (D), R22.1
BL_PWM: R32.1, U9.4 (CTRL); also elsewhere on the board
BL_SW: D6.2 (A), L2.2, U9.1 (SW)
BOOST_IN: C29.1, L1.1, Q1.3 (D), U7.4 (EN), U7.5 (VIN)
CP_N: C36.2, D4.3 (COM)
CP_P: C33.2, D2.3 (COM)
GND: C27.2, C28.2, C29.2, C31.2, C32.2, C34.2, C35.2, C37.2, C38.2, C39.2, C40.2, C41.2, C42.2, C43.2, D3.2 (A), D4.2 (K), D5.1 (K), J3.5, J3.36, J3.38, J3.48, J3.MP (MountPin), Q2.2 (S), R20.2, R21.2, R23.2, R25.2, R29.2, R31.2, R32.2, U7.2 (GND), U8.2 (V-), U9.2 (GND); also elsewhere on the board
LCD_B0: J3.19; also elsewhere on the board
LCD_B1: J3.18; also elsewhere on the board
LCD_B2: J3.17; also elsewhere on the board
LCD_B3: J3.16; also elsewhere on the board
LCD_B4: J3.15; also elsewhere on the board
LCD_B5: J3.14; also elsewhere on the board
LCD_B6: J3.13; also elsewhere on the board
LCD_B7: J3.12; also elsewhere on the board
LCD_DCLK: J3.37; also elsewhere on the board
LCD_DE: J3.9; also elsewhere on the board
LCD_DITHB: J3.47, R18.1
LCD_G0: J3.27; also elsewhere on the board
LCD_G1: J3.26; also elsewhere on the board
LCD_G2: J3.25; also elsewhere on the board
LCD_G3: J3.24; also elsewhere on the board
LCD_G4: J3.23; also elsewhere on the board
LCD_G5: J3.22; also elsewhere on the board
LCD_G6: J3.21; also elsewhere on the board
LCD_G7: J3.20; also elsewhere on the board
LCD_HS: J3.11, R16.1
LCD_LR: J3.39, R19.1; also elsewhere on the board
LCD_MODE: J3.8, R15.1
LCD_R0: J3.35; also elsewhere on the board
LCD_R1: J3.34; also elsewhere on the board
LCD_R2: J3.33; also elsewhere on the board
LCD_R3: J3.32; also elsewhere on the board
LCD_R4: J3.31; also elsewhere on the board
LCD_R5: J3.30; also elsewhere on the board
LCD_R6: J3.29; also elsewhere on the board
LCD_R7: J3.28; also elsewhere on the board
LCD_RST: J3.44, R21.1; also elsewhere on the board
LCD_UD: J3.40, R20.1; also elsewhere on the board
LCD_VS: J3.10, R17.1
VCOM: C40.1, J3.6, J3.46, R30.2; also elsewhere on the board
VCOM_BOT: R29.1, RV1.3
VCOM_BUF: R30.1, U8.3 (-), U8.4
VCOM_SET: C39.1, RV1.2, U8.1 (+)
VCOM_TOP: R28.2, RV1.1
VGH: C35.1, D3.1 (K), J3.41, R26.2; also elsewhere on the board
VGH_RAW: C34.1, D2.2 (K), R26.1
VGL: C38.1, D5.2 (A), J3.42, R27.2; also elsewhere on the board
VGL_RAW: C37.1, D4.1 (A), R27.1
VLED_A: C42.1, D6.1 (K), J3.1, J3.2
VLED_K: J3.3, J3.4, R31.1, U9.3 (FB)

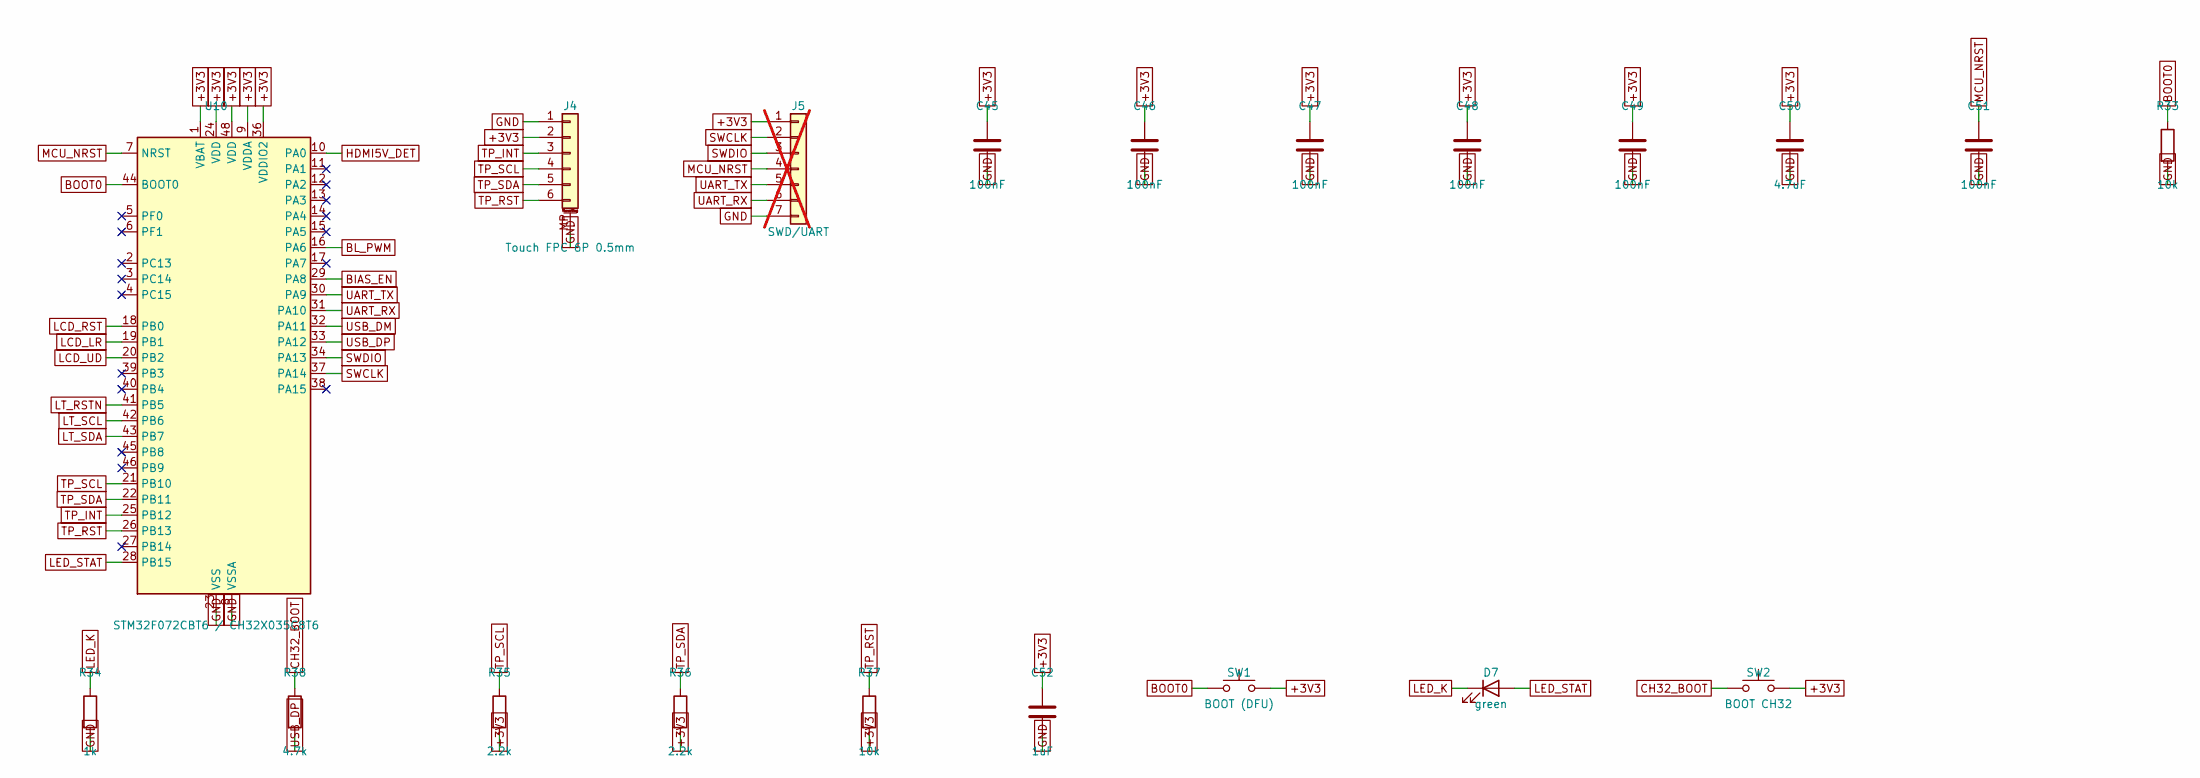
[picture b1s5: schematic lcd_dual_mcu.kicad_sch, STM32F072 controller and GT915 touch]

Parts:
C45, C46, C47, C48, C49, C51: 100nF; C_0603_1608Metric; LCSC C14663
C50: 4.7uF; C_0603_1608Metric
C52: 1uF; C_0603_1608Metric; LCSC C15849
D7: green; LED_0603_1608Metric
J4: Touch FPC 6P 0.5mm; Hirose_FH12-6S-0.5SH_1x06-1MP_P0.50mm_Horizontal; MPN Hirose FH12-6S-0.5SH (check contact sid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
J5: SWD/UART; PinHeader_1x07_P1.27mm_Vertical; not fitted
R33, R37: 10k; R_0603_1608Metric; LCSC C25804
R34: 1k; R_0603_1608Metric; LCSC C21190
R35, R36: 2.2k; R_0603_1608Metric
R38: 4.7k; R_0603_1608Metric; LCSC C23162
SW1: BOOT (DFU); SW_SPST_B3U-1000P; MPN Omron B3U-1000P
SW2: BOOT CH32; SW_SPST_B3U-1000P; MPN Omron B3U-1000P
U10: STM32F072CBT6 / CH32X035C8T6; LQFP-48_7x7mm_P0.5mm; MPN STM32F072CBT6 (or CH32X035C8T6, same fo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

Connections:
+3V3: C45.1, C46.1, C47.1, C48.1, C49.1, C50.1, C52.1, J4.2, J5.1, R35.2, R36.2, R37.2, SW1.2, SW2.2, U10.1 (VBAT), U10.9 (VDDA), U10.24 (VDD), U10.36 (VDDIO2), U10.48 (VDD); also elsewhere on the board
BIAS_EN: U10.29 (PA8); also elsewhere on the board
BL_PWM: U10.16 (PA6); also elsewhere on the board
BOOT0: R33.1, SW1.1, U10.44 (BOOT0)
CH32_BOOT: R38.1, SW2.1
GND: C45.2, C46.2, C47.2, C48.2, C49.2, C50.2, C51.2, C52.2, J4.1, J4.MP (MountPin), J5.7, R33.2, R34.2, U10.8 (VSSA), U10.23 (VSS), U10.35 (VSS), U10.47 (VSS); also elsewhere on the board
HDMI5V_DET: U10.10 (PA0); also elsewhere on the board
LCD_LR: U10.19 (PB1); also elsewhere on the board
LCD_RST: U10.18 (PB0); also elsewhere on the board
LCD_UD: U10.20 (PB2); also elsewhere on the board
LED_K: D7.1 (K), R34.1
LED_STAT: D7.2 (A), U10.28 (PB15)
LT_RSTN: U10.41 (PB5); also elsewhere on the board
LT_SCL: U10.42 (PB6); also elsewhere on the board
LT_SDA: U10.43 (PB7); also elsewhere on the board
MCU_NRST: C51.1, J5.4, U10.7 (NRST)
SWCLK: J5.2, U10.37 (PA14)
SWDIO: J5.3, U10.34 (PA13)
TP_INT: J4.3, U10.25 (PB12)
TP_RST: J4.6, R37.1, U10.26 (PB13)
TP_SCL: J4.4, R35.1, U10.21 (PB10)
TP_SDA: J4.5, R36.1, U10.22 (PB11)
UART_RX: J5.6, U10.31 (PA10)
UART_TX: J5.5, U10.30 (PA9)
USB_DM: U10.32 (PA11); also elsewhere on the board
USB_DP: R38.2, U10.33 (PA12); also elsewhere on the board
